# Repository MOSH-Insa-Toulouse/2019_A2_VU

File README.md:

# Diep VU Group 5ISS_A2 2019-2020
KiCad Project
-------------

This is my very first Arduino Shield realised on KiCad for a Smart Gas Sensor. 
This smart gas sensor has been realised in AIME laboratory at INSA Toulouse.
Please find bellow an overview of my Arduino Shield.

First of the 3D view of the final shield :

This shield is composed by the following elements:

Arduino connections :

It is a model generated directly from KiCad Software, I used it as the base of my shield.

Amplifier Stage :

This element allows us to amplifiy the signal before going through the analog to digital convesion of the Arduino.

Gas Sensor AIME :

This element is the main component of the project. It has 4 pins for Gas detections (2 pins for each gas) and 2 pins for temperature sensor.

And finally the PCB:

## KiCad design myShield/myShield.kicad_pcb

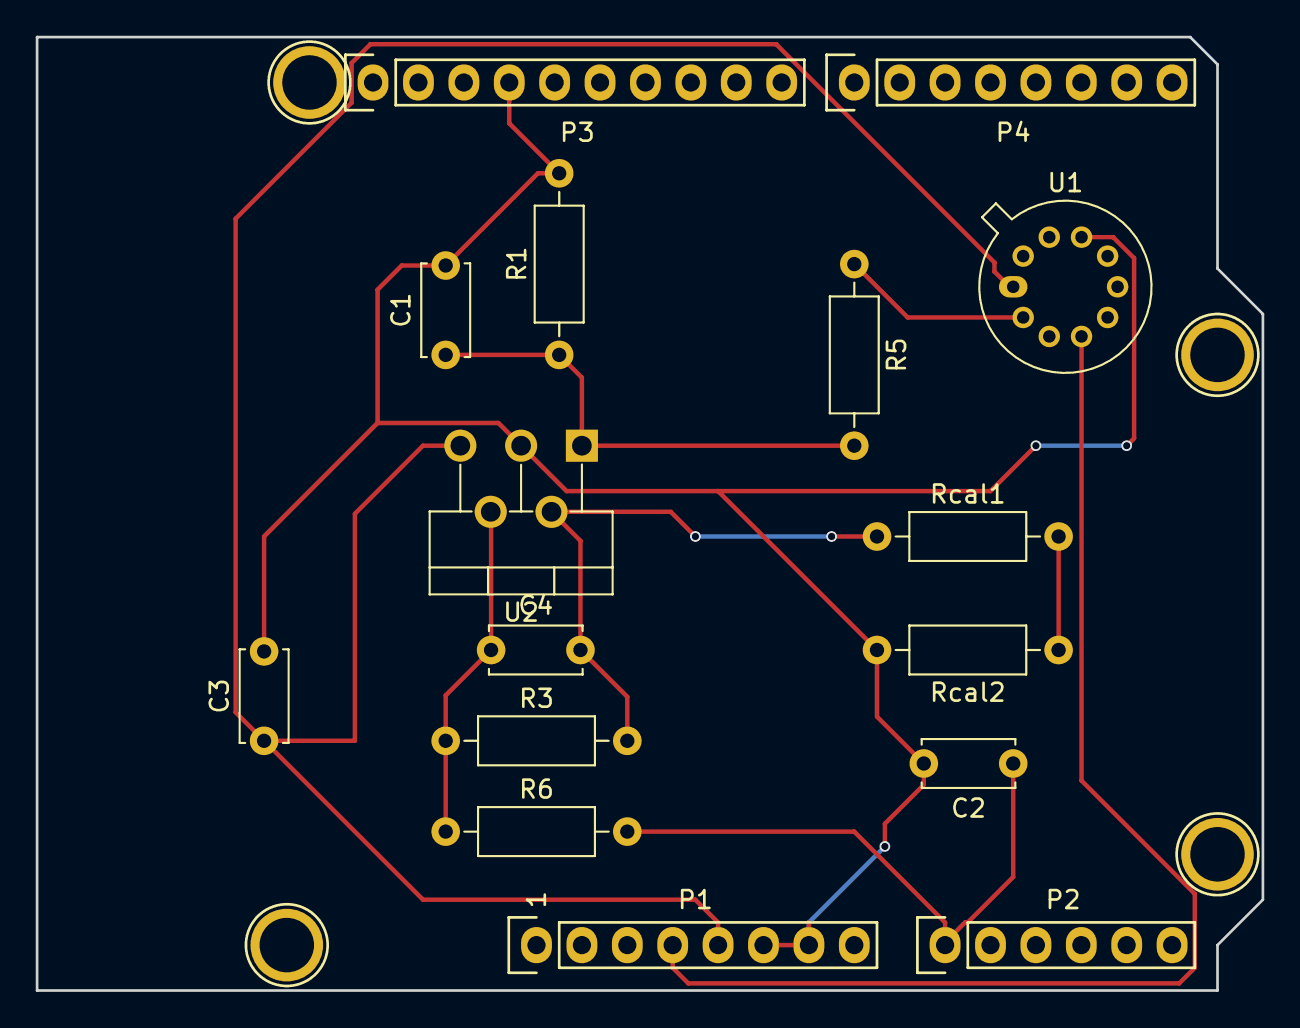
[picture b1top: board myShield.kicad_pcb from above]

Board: 2 copper layers, 68.6 x 53.3 mm, 20 parts (0 on the bottom side), 9 nets.

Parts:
C1, C2, C3: 100n; C_Disc_D5.0mm_W2.5mm_P5.00mm
C4: 1u; C_Disc_D5.0mm_W2.5mm_P5.00mm
P1: Power; Socket_Strip_Arduino_1x08
P2: Analog; Socket_Strip_Arduino_1x06
P3: Digital; Socket_Strip_Arduino_1x10
P4: Digital; Socket_Strip_Arduino_1x08
P5, P6, P7, P8: CONN_01X01; Arduino_1pin
R1, R3: 100k; R_Axial_DIN0207_L6.3mm_D2.5mm_P10.16mm_Horizontal
R5: 10k; R_Axial_DIN0207_L6.3mm_D2.5mm_P10.16mm_Horizontal
R6: 1k; R_Axial_DIN0207_L6.3mm_D2.5mm_P10.16mm_Horizontal
Rcal1, Rcal2: 100k; R_Axial_DIN0207_L6.3mm_D2.5mm_P10.16mm_Horizontal
U1: GasAIME; TO-5-10
U2: LM1875; TO-220-5_P3.4x3.7mm_StaggerOdd_Lead3.8mm_Vertical

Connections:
+3V3: P1.4, U1.4
+5V: C3.1, P1.5, U1.1, U2.5
ANx.Arduino: C2.1, P2.1, R6.2
GND: C1.2, C2.2, C3.2, P1.6, P1.7, P3.4, R1.2, Rcal2.2, U1.8, U2.3
unnamed: C1.1, R1.1, R5.2, U2.1
unnamed: C4.1, R3.1, R6.1, U2.4
unnamed: C4.2, R3.2, Rcal1.1, U2.2
unnamed: R5.1, U1.2
unnamed: Rcal1.2, Rcal2.1
